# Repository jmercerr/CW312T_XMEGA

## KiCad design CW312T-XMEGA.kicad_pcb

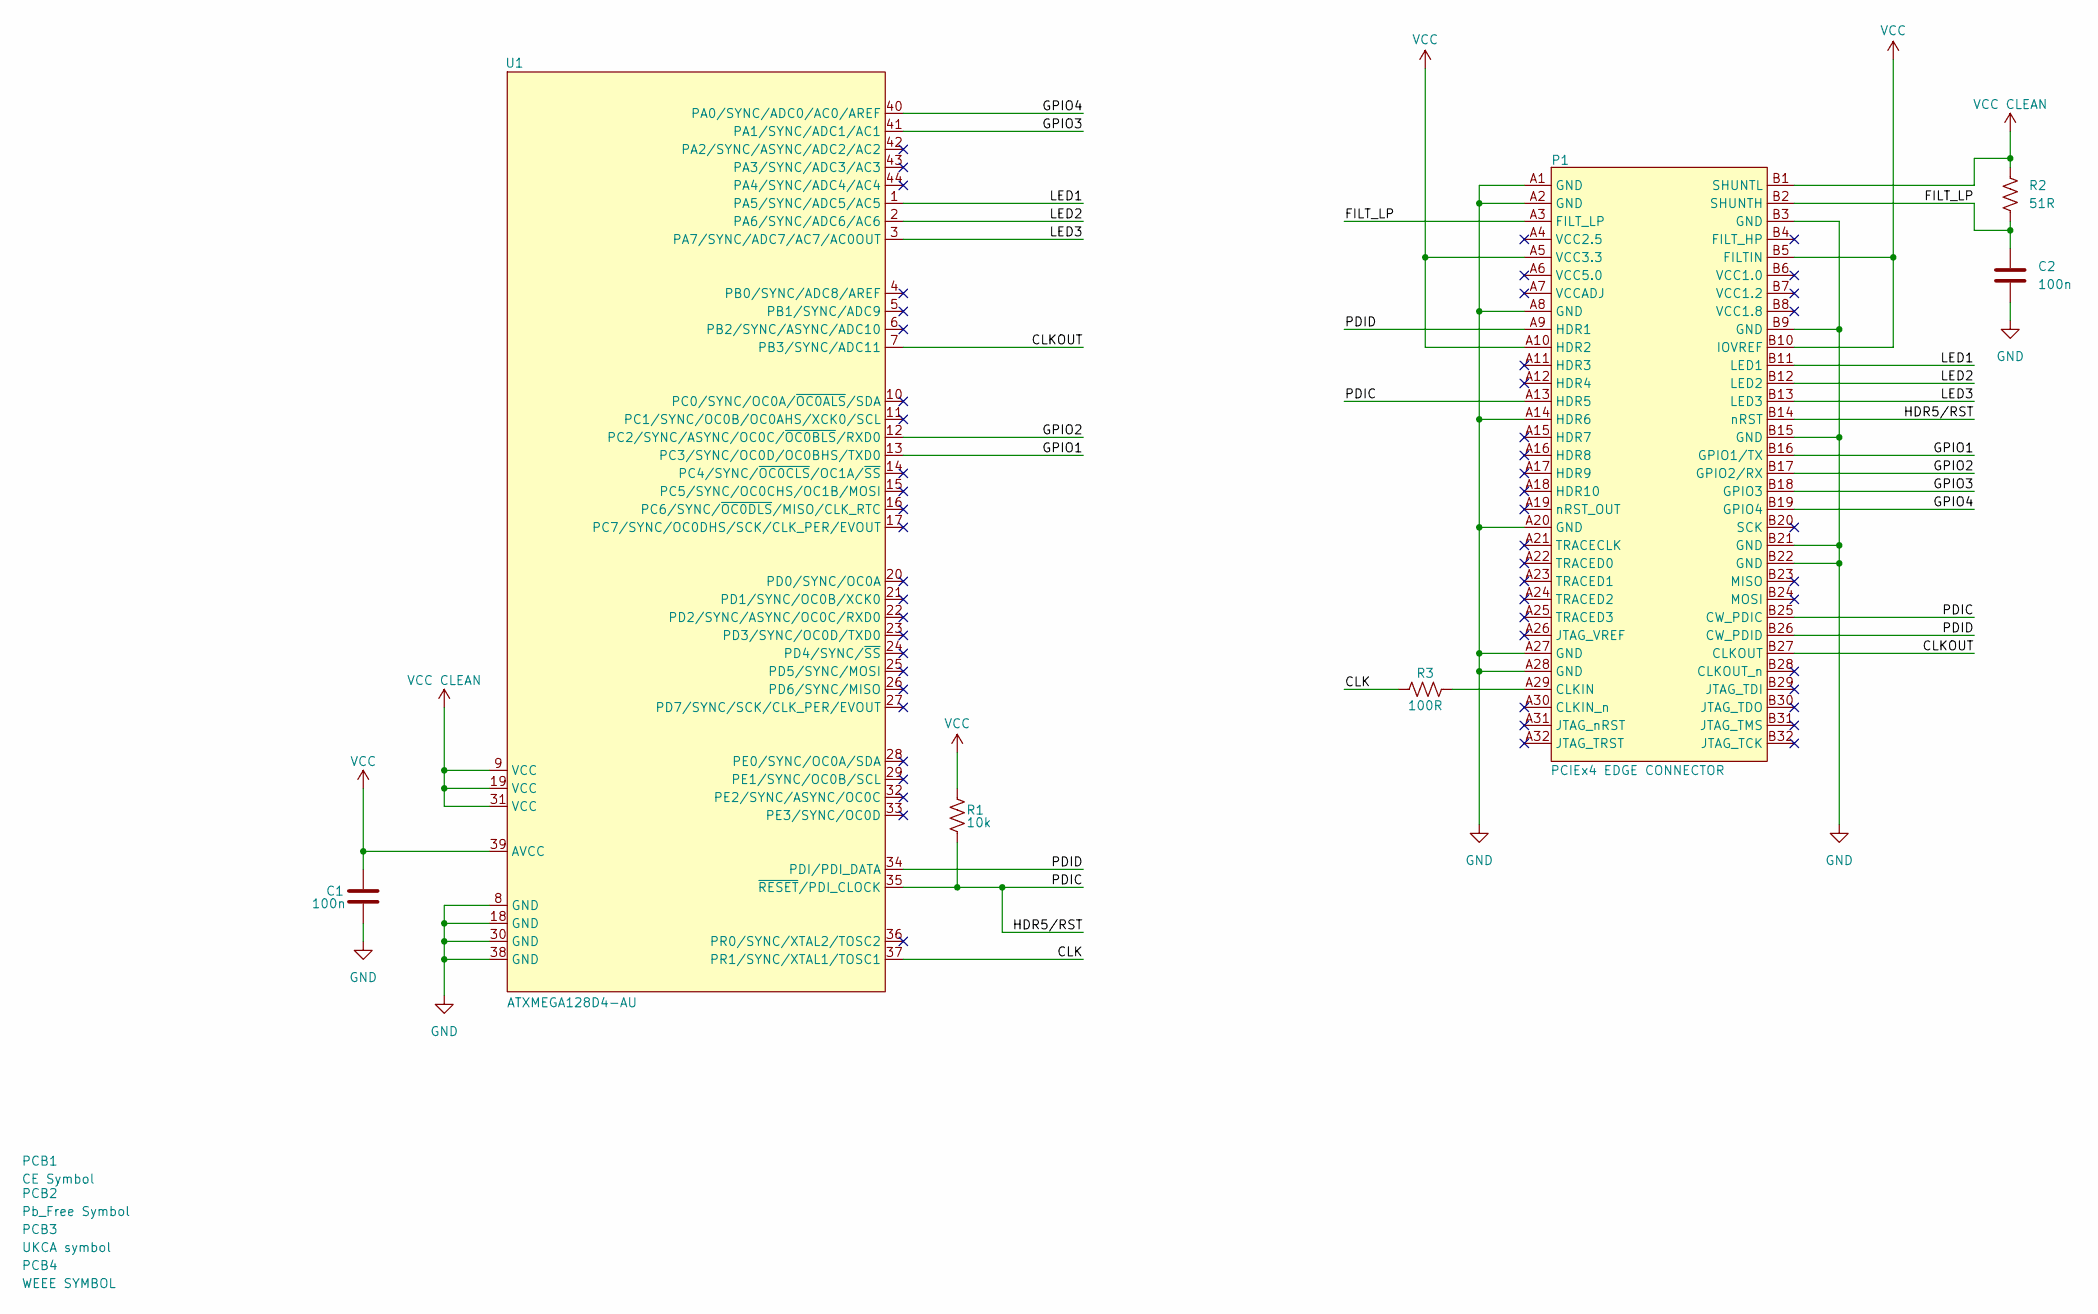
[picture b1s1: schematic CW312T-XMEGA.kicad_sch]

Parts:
C1, C2: CAP_100n_6.3V_0603; C_0603_1608Metric; Manufacturer Part Number CC0603KRX7R5BB104
P1: PCIEx4 EDGE CONNECTOR; CW312_Template
PCB1: CE Symbol; CE-Logo_8.5x6mm_SilkScreen
PCB2: Pb_Free Symbol; Pb_Free_8.0x8.0mm_SilkScreen
PCB3: UKCA symbol; UKCA-Logo_8x8mm_SilkScreen
PCB4: WEEE SYMBOL; WEEE-Logo_5.6x8mm_SilkScreen
R1: RES_10k_0603; R_0603_1608Metric; Manufacturer Part Number RC0603FR-0710KL
R2: RES_51R_0603; R_0603_1608Metric; Manufacturer Part Number RC0603FR-0751RL
R3: RES_100R_0603; R_0603_1608Metric; Manufacturer Part Number RC0603FR-07100RL
U1: ATXMEGA128D4-AU; TQFP-44_10x10mm_P0.8mm; Manufacturer Part Number ATXMEGA128D4-AU

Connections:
/CLK: R3.1, U1.37 (PR1/SYNC/XTAL1/TOSC1)
/CLKOUT: P1.B27 (CLKOUT), U1.7 (PB3/SYNC/ADC11)
/FILT_LP: C2.1, P1.A3 (FILT_LP), P1.B2 (SHUNTH), R2.1
/GPIO1: P1.B16 (GPIO1/TX), U1.13 (PC3/SYNC/OC0D/OC0BHS/TXD0)
/GPIO2: P1.B17 (GPIO2/RX), U1.12 (PC2/SYNC/ASYNC/OC0C/~OC0BLS/RXD0)
/GPIO3: P1.B18 (GPIO3), U1.41 (PA1/SYNC/ADC1/AC1)
/GPIO4: P1.B19 (GPIO4), U1.40 (PA0/SYNC/ADC0/AC0/AREF)
/HDR5/RST: P1.A13 (HDR5), P1.B14 (nRST), P1.B25 (CW_PDIC), R1.1, U1.35 (~RESET/PDI_CLOCK)
/LED1: P1.B11 (LED1), U1.1 (PA5/SYNC/ADC5/AC5)
/LED2: P1.B12 (LED2), U1.2 (PA6/SYNC/ADC6/AC6)
/LED3: P1.B13 (LED3), U1.3 (PA7/SYNC/ADC7/AC7/AC0OUT)
/PDID: P1.A9 (HDR1), P1.B26 (CW_PDID), U1.34 (PDI/PDI_DATA)
GND: C1.1, C2.2, P1.A1 (GND), P1.A2 (GND), P1.A8 (GND), P1.A14 (HDR6), P1.A20 (GND), P1.A27 (GND), P1.A28 (GND), P1.B3 (GND), P1.B9 (GND), P1.B15 (GND), P1.B21 (GND), P1.B22 (GND), U1.8 (GND), U1.18 (GND), U1.30 (GND), U1.38 (GND)
unnamed: P1.A29 (CLKIN), R3.2
VCC: C1.2, P1.A5 (VCC3.3), P1.A10 (HDR2), P1.B5 (FILTIN), P1.B10 (IOVREF), R1.2, U1.39 (AVCC)
VCC CLEAN: P1.B1 (SHUNTL), R2.2, U1.9 (VCC), U1.19 (VCC), U1.31 (VCC)

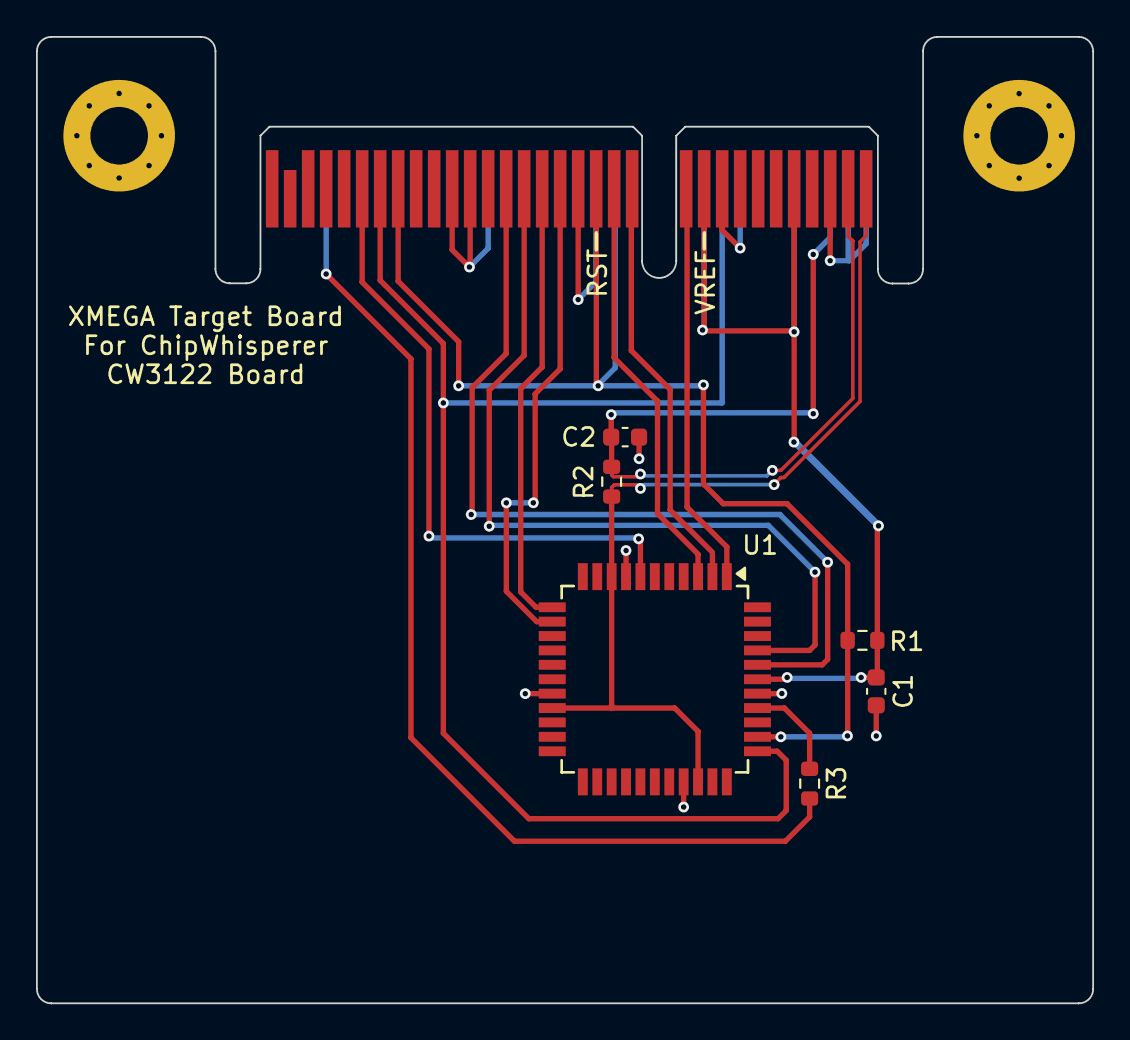
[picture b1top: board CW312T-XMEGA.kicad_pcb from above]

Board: 2 copper layers, 58.7 x 53.7 mm, 11 parts (0 on the bottom side), 16 nets.

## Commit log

2024-11-18 Draft of CW312T-XMEGA target - ready for review
2024-11-18 added production files
2024-11-22 updated silkscreen and schematic
2024-11-22 updated cw312t template and production files
2024-12-03 updated schematic and pcb - Ready for review
2024-12-04 updated power on schematic and routing, updated silkscreen
2024-12-19 updated schematic and pcb, after library reorganization
